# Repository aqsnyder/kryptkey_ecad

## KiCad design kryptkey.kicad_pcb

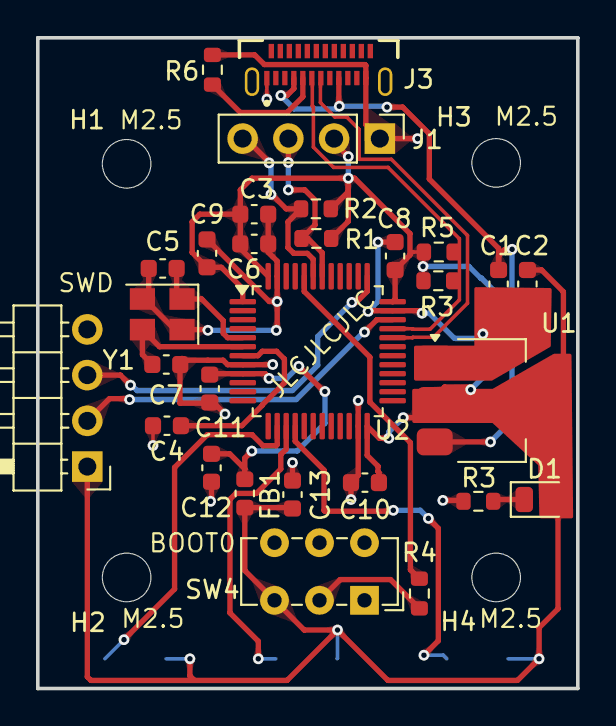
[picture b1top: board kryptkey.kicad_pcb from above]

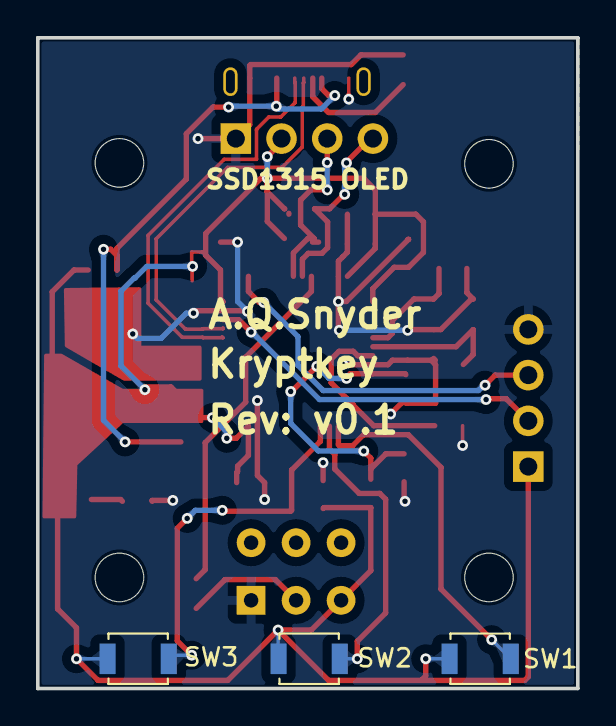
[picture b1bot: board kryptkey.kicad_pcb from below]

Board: 2 copper layers, 30.0 x 36.2 mm, 36 parts (3 on the bottom side), 20 nets.

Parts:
C1, C2: 22uF; C_0603_1608Metric
C3: 10uF; C_0603_1608Metric
C4, C6, C8, C9, C10: 100nF; C_0603_1608Metric
C5, C7: 10pF; C_0603_1608Metric
C11: 10nF; C_0603_1608Metric
C12, C13: 1uF; C_0603_1608Metric
D1: LED_RED; LED_0805_2012Metric
FB1: 120R; L_0603_1608Metric
H1: M1_OLED; MountingHole_2.7mm_M2.5
H2: M3_OLED; MountingHole_2.7mm_M2.5
H3: M2_OLED; MountingHole_2.7mm_M2.5
H4: M4_OLED; MountingHole_2.7mm_M2.5
J1: Conn_01x04_Pin; PinHeader_1x04_P2.54mm_Vertical
J2: Conn_01x04_Pin; PinHeader_1x04_P2.54mm_Horizontal
J3: USB4155-03-C_REVA; GCT_USB4155-03-C_REVA
R1, R2, R3, R3#2, R5: 1.5K; R_0603_1608Metric
R4: 10K; R_0603_1608Metric
R6: 5.1K; R_0603_1608Metric
SW1, SW2, SW3: SW_Push; SW_SPST_B3U-1000P
SW4: SW_SPDT; SW_E-Switch_EG1271_SPDT
U1: AMS1117-3.3; SOT-223-3_TabPin2
U2: STM32F103C8T6; LQFP-48_7x7mm_P0.5mm
Y1: 16MHz; Crystal_SMD_3225-4Pin_3.2x2.5mm

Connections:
+3V3: C2.1, C3.1, C6.1, C8.1, C9.1, C10.1, C13.1, D1.2 (A), FB1.2, J1.2, J2.1, R1.2, R2.2, R3#2.1, R5.2, SW1.2, SW2.2, SW3.2, SW4.3 (C), U1.2 (VO), U2.1 (VBAT), U2.24 (VDD), U2.36 (VDD), U2.48 (VDD)
+3V3_A: C11.1, C12.1, FB1.1, U2.9 (VDDA)
/BOOT0: R4.2, U2.44 (BOOT0)
/HSE_IN: C5.1, U2.5 (PD0), Y1.1
/HSE_OUT: C7.1, U2.6 (PD1), Y1.3
/I2C1_SCL_OLED: J1.3, R1.1, U2.42 (PB6)
/I2C1_SDA_OLED: J1.4, R2.1, U2.43 (PB7)
/NRST: C4.1, U2.7 (NRST)
/PWR_LED_K: D1.1 (K), R3.2
/SWCLK: J2.3, U2.37 (PA14)
/SWDIO: J2.2, U2.34 (PA13)
/SW_BOOT0: R4.1, SW4.2 (B)
/UI_DOWN_BUTTON: SW1.1, U2.14 (PA4)
/UI_ENTER_BUTTON: SW2.1, U2.15 (PA5)
/UI_UP_BUTTON: SW3.1, U2.16 (PA6)
/USB_D+: J3.A6 (DP1), R3#2.2, R5.1, U2.33 (PA12)
/USB_D-: J3.A7 (DN1), U2.32 (PA11)
GND: C1.2, C2.2, C3.2, C4.2, C5.2, C6.2, C7.2, C8.2, C9.2, C10.2, C11.2, C12.2, C13.2, J1.1, J2.4, J3.A1 (GND_A), J3.A12 (GND_A), R3.1, R6.1, SW4.1 (A), U1.1 (GND), U2.8 (VSSA), U2.23 (VSS), U2.35 (VSS), U2.47 (VSS), Y1.2, Y1.4
unnamed: J3.A5 (CC1), R6.2
VBUS: C1.1, J3.A4 (VBUS_A), J3.A9 (VBUS_A), U1.3 (VI)

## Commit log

2024-09-23 worked on board layout
2024-09-23 first pass routing
2024-09-23 error free DRC
2024-09-25 final mounting hole possitions and flipped UI botton side
2024-09-25 spaced UI button vias off of the pads for solder drainage prevention
2024-09-25 v0.1 jlcpcb production order
2024-09-26 begin edits for v0.2 - added teardrops
